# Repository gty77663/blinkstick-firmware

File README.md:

# BlinkStick Firmware

BlinkStick is a DIY open source USB RGB LED Controller. Original idea is to create a little & handy RGB stick, and make its code and protocol opensource, so everybody can enjoy playing with RGB LEDs using the programming launguage or application of your choise. It's small, the biggest model is the size of a credit card and supports both popular types of RGB LEDs - generic 12V ones and addressable WS2812. 

You can find more details about it here:

http://www.blinkstick.com

This branch contains the firmware,  required for the BlinkStick Pro, based around ATTiny45/85 chip.

- [BlinkStick Firmware](#blinkstick-firmware)
  - [BlinkStick types](#blinkstick-types)
  - [Serial number](#serial-number)
  - [BlinkStick communication protocol](#blinkstick-communication-protocol)
  - [EEPROM memory map](#eeprom-memory-map)
  - [How to build the firmware](#how-to-build-the-firmware)
    - [Windows](#windows)
    - [Linux](#linux)
    - [Mac-OS](#mac-os)
    - [Compiling](#compiling)
  - [TODO](#todo)
  - [License](#license)

## BlinkStick types
| Name                   | Description                                                                                                        | Link                                                          |
|------------------------|--------------------------------------------------------------------------------------------------------------------|---------------------------------------------------------------|
| BlinkStick             | Small formfactor of a USB stick with one WS2812 LED onboard, comes as a DIY kit.                                   | [here](https://www.blinkstick.com/products/blinkstick)        |
| BlinkStick Pro         | USB stick-sized controller board for generic RGB and WS2812 LED strips.                                            | [here](https://www.blinkstick.com/products/blinkstick-pro)    |
| BlinkStick Square      | Little handy square with 8 WS2812 LEDs and a micro-USB port.                                                       | [here](https://www.blinkstick.com/products/blinkstick-square) |
| BlinkStick Strip(mini) | Eight(4 for the mini version) WS2812LEDs shaped in one line & a micro-USB port.                                    | [here](https://www.blinkstick.com/products/blinkstick-strip)  |
| BlinkStick Nano        | Just like normal BlinkStick, but smaller, comes preassembled and has two WS2812 LEDs instead of one.               | [here](https://www.blinkstick.com/products/blinkstick-nano)   |
| BlinkStick Flex        | Really small formfactor with a micro-USB port that supports up to 32 WS2812 LEDs in a strip.                       | [here](https://www.blinkstick.com/products/blinkstick-flex)   |
| BlinkStick L3          | Combines BlinkStick Pro and LED Adapter to control normal, 12V RGB strips.                                         | [here](https://www.blinkstick.com/products/blinkstick-l3)     |
| BlinkStick Advanced    | Combines both generic RGB and WS2812 controllers in a very small formfactor to act as a universal LED strips tool. | none for now                                                  |

## Serial number
Each BlinkStick has a unique serial number 12-byte long serial number, that consist of "BS" header, that stands for "BlinksStick",
followed by its index number, 6 symbols length. The footer is 4 bytes long, that signify the BlinkStick version it is.  
Ex: BS123456-1.0  
```
BSnnnnnn-1.0
||  |    | |- Software minor version
||  |    |--- Software major version
||  |-------- Denotes sequential number
||----------- Denotes BlinkStick device
```
Possible BlinkStick version are:  
* 1.x - BlinkStick
* 2.x - BlinkStick Pro
* 3.x - BlinkStick Square/Strip/Nano/Flex   
This are differentiate by the device version, aka firmware version.  

| Version | Description       | N. of LEDs |
|---------|-------------------|------------|
| 0x200   | BlinkStick Square | 8          |
| 0x201   | BlinkStick Strip  | 8          |
| 0x202   | BlinkStick Nano   | 2          |
| 0x203   | BlinkStick Flex   | ≤32        |
* 4.x - BlinkStick Advanced

## BlinkStick communication protocol

BlinkStick is controller via HID USB reports, each report has its unique id and is responsible for its specific purpose:  

| Report ID | Description                                                                                                    | Format                      |
|-----------|----------------------------------------------------------------------------------------------------------------|-----------------------------|
| 1         | Set\get RGB strip color or first ARGB LED color on first channel                                               | [R, G, B]                   |
| 2         | Set\read the name of the BlinkStick                                                                            | [Binary Data 0..32]         |
| 3         | Set\read custom data stored in BlinkStick's EEPROM                                                             | [Binary Data 0..32]         |
| 4         | Set\read current mode: 0 - RGB LED Strip, 1 - Inverse RGB LED Strip, 2 - WS2812, 3 - Advanced (WS2812 and RGB) | [MODE]                      |
| 5         | Set\read the value of one single ARGB LED on specified channel with INDEX                                      | [CHANNEL, INDEX, R, G, B]   |
| 6         | Set\read LED  from 0 to x (x≤7), on specified channel                                                          | [Channel, [G, R, B][0..7]]  |
| 7         | Set\read LED colors from 0 to x (x≤15), on specified channel                                                   | [Channel, [G, R, B][0..15]] |
| 8         | Set\read LED colors from 0 to x (x≤31), on specified channel                                                   | [Channel, [G, R, B][0..31]] |
| 9         | Set\read LED colors from 0 to x (x≤63), on specified channel                                                   | [Channel, [G, R, B][0..63]] |

## EEPROM memory map 
BlinkStick uses EEPROM to store some of power sensitive data, such as its Name, Serial, etc. 
  
| Name             | Description |
|------------------|-------------|
| Address          | Use         |
| 0x00             | *unused*    |
| 0x01-0x0C        | **Serial**  |
| 0x0D             | **Mode**    |
| 0x0F-0x1F        | *unused*    |
| 0x20-0x3F        | **Name**    |
| 0x40-0x5F        | **Data**    |
| 0x60-0xFF(0x1ff) | *unused*    |

## How to build the firmware

### Windows   
* You'll need to install and add to system path [AVR-GCC toolchain](https://www.microchip.com/en-us/tools-resources/develop/microchip-studio/gcc-compilers)
* [Python3](https://www.python.org/downloads/)
* And [Make](https://www.gnu.org/software/make/#download) on you system. 

### Linux  
#### AVR-GCC toolchain  
    sudo apt-get update  
    sudo apt-get upgrade all
    sudo apt-get install gcc-avr binutils-avr avr-libc  

#### Python  
    sudo apt install python3 python3-pip
#### Make    
    sudo apt install make

### Mac-OS
#### AVR-GCC toolchain
First, you need to install HomeBrew:  

    ruby -e "$(curl -fsSL https://raw.githubusercontent.com/Homebrew/install/master/install)"

Then you can install avr toolchain, by typing two following commands:
First tap the repository:

    brew tap osx-cross/avr`

Then install the latest version of avr-libc (version 4.9.2 at the time of writing):

    brew install avr-libc

#### Python
You can download it from [python official site](https://www.python.org/downloads/macos/).

#### Make 
If you allready installed brew, paste this command in the terminal:

    brew install make

### Compiling
After installing all nessecery software, you can run make in project folder and choose one of the options that you need:
```
"This Makefile has no default rule. Use one of the following:"
"make hex ....... to build main.hex"
"make program ... to flash fuses and firmware"
"make fuse ...... to flash the fuses"
"make flash ..... to flash the firmware (use this on metaboard)"
"make dump ...... dump eeprom"
"make dumpflash . dump flash"
"make defaults .. write default eeprom"
"make clean ..... to delete objects and hex file"
"make deploy .... program, increment serial, defaults"
```

## TODO  
* Add BlinkStick devices support to SignalRGB
* Add BlinkStick devices support to OpenRGB
* Optional, maybe add built-in effects and animations, 

## License

Released under CC-BY-NC-SA 3.0 license:

http://creativecommons.org/licenses/by-nc-sa/3.0/

(c) 2013 by Agile Innovative Ltd  
(c) 2023 by gty77663

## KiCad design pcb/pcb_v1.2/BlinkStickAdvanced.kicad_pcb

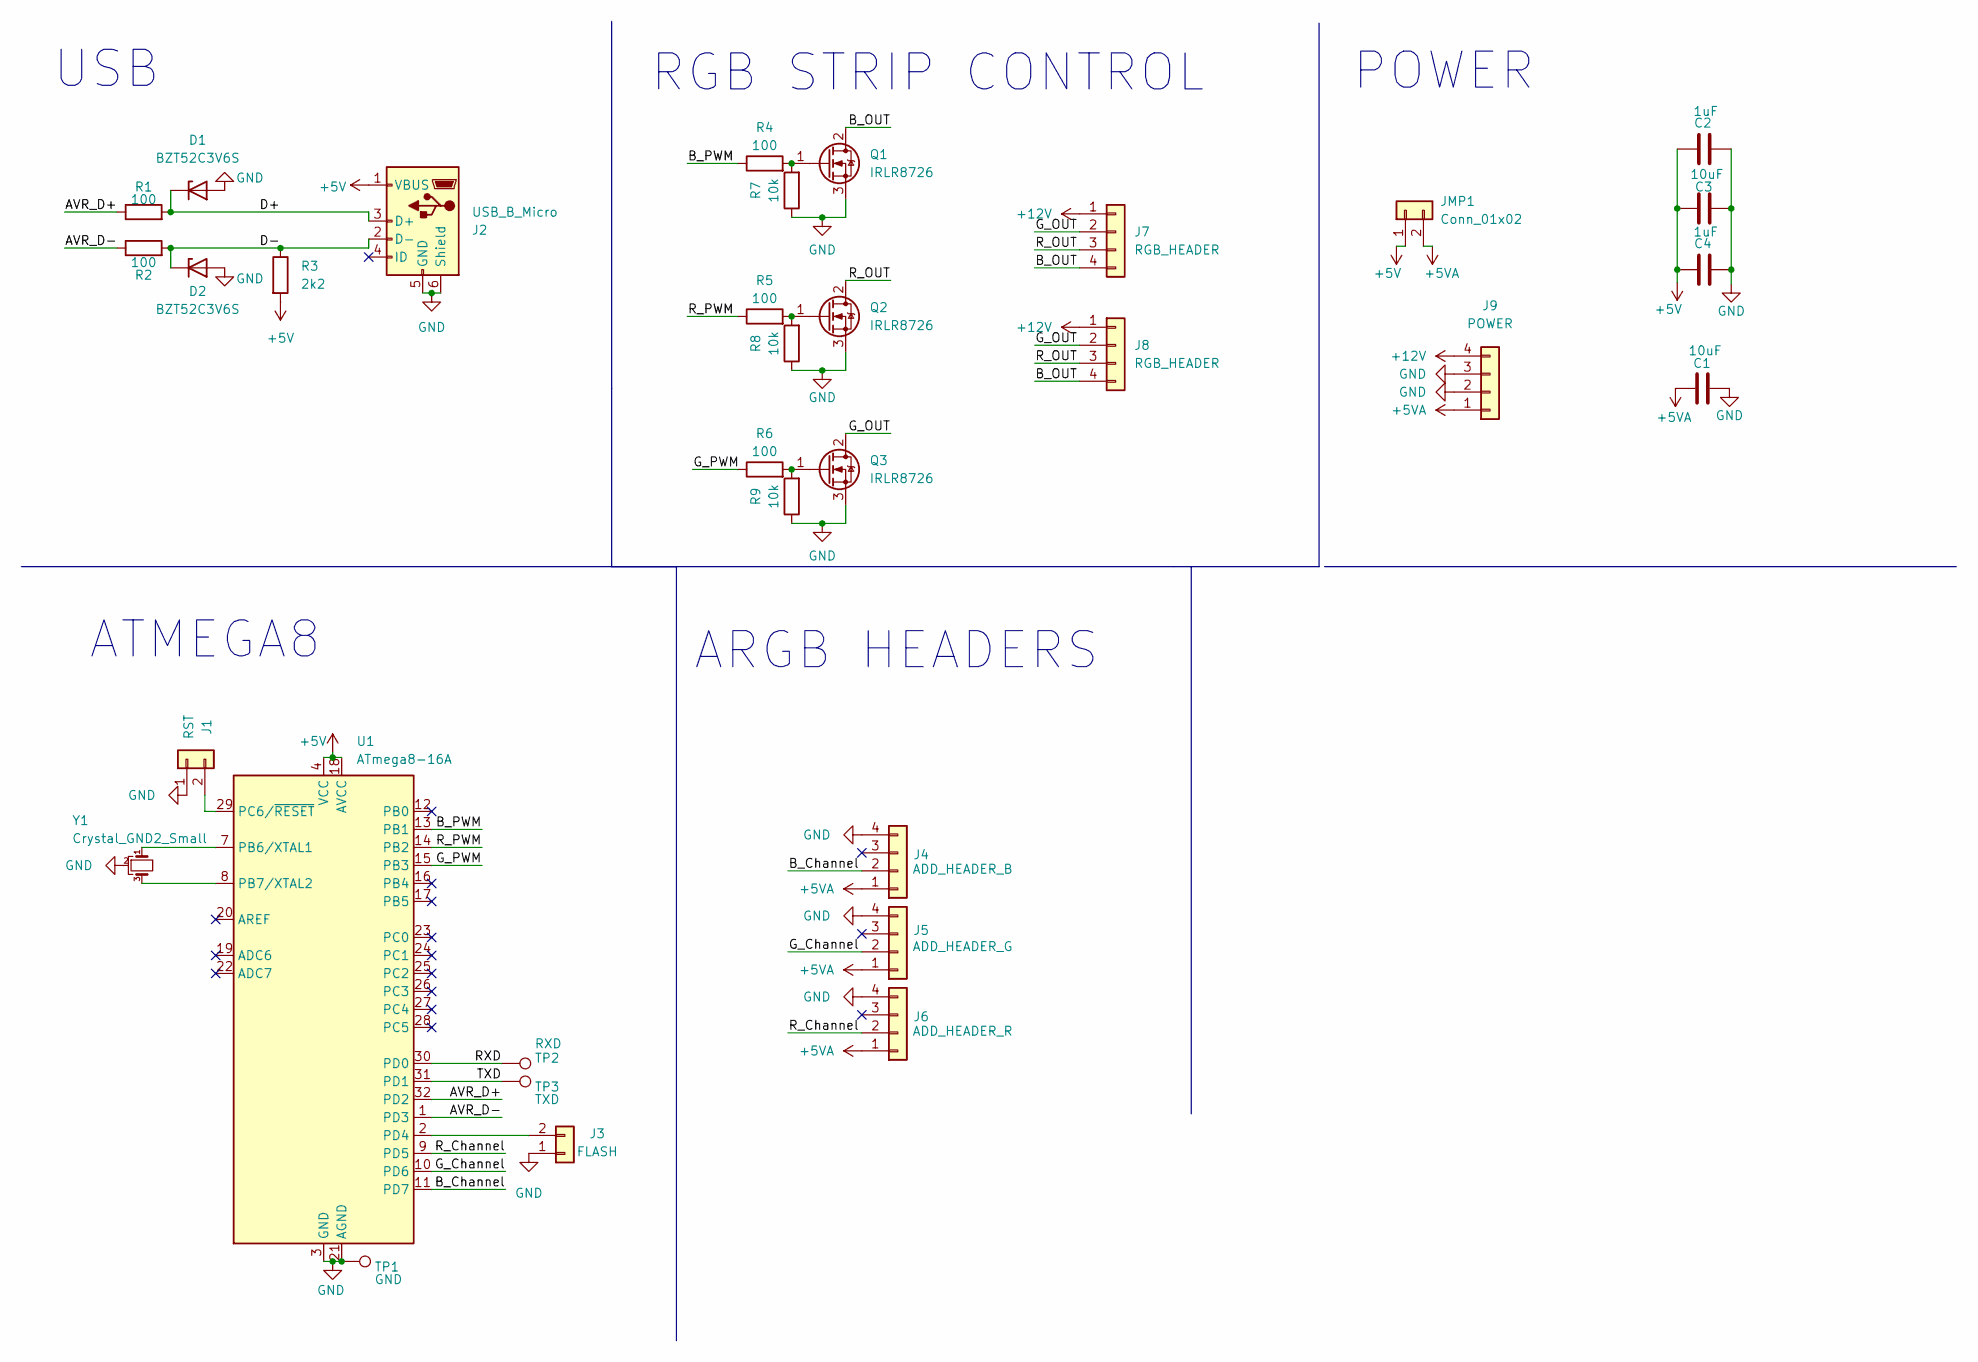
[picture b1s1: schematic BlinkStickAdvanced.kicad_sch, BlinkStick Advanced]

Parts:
C1, C3: 10uF; C_0603_1608Metric_Pad1.08x0.95mm_HandSolder
C2, C4: 1uF; C_0603_1608Metric_Pad1.08x0.95mm_HandSolder
D1, D2: BZT52C3V6S; D_SOD-323
J1: RST; PinHeader_1x02_P2.54mm_Vertical
J2: USB_B_Micro; USB_Micro-B_Molex-105017-0001
J3: FLASH; PinHeader_1x02_P2.54mm_Vertical
J4: ADD_HEADER_B; PinHeader_1x04_P2.54mm_Vertical
J5: ADD_HEADER_G; PinHeader_1x04_P2.54mm_Vertical
J6: ADD_HEADER_R; PinHeader_1x04_P2.54mm_Vertical
J7, J8: RGB_HEADER; PinHeader_1x04_P2.54mm_Vertical
J9: POWER; JST_XH_B4B-XH-A_1x04_P2.50mm_Vertical
JMP1: Conn_01x02; PinHeader_1x02_P2.54mm_Vertical
Q1, Q2, Q3: IRLR8726; TO-263-2
R1, R2, R4, R5, R6: 100; R_0603_1608Metric_Pad0.98x0.95mm_HandSolder
R3: 2k2; R_0603_1608Metric_Pad0.98x0.95mm_HandSolder
R7, R8, R9: 10k; R_0603_1608Metric_Pad0.98x0.95mm_HandSolder
TP1: GND; TestPoint_Pad_D1.5mm
TP2: RXD; TestPoint_Pad_D1.5mm
TP3: TXD; TestPoint_Pad_D1.5mm
U1: ATmega8-16A; TQFP-32_7x7mm_P0.8mm
Y1: Crystal_GND2_Small; Resonator_SMD_Murata_CSTxExxV-3Pin_3.0x1.1mm

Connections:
+5V: C2.2, C3.2, C4.2, J2.1 (VBUS), JMP1.1, R3.2, U1.4 (VCC), U1.6 (VCC), U1.18 (AVCC)
+5VA: C1.2, J4.1, J5.1, J6.1, J9.1, JMP1.2
+12V: J7.1, J8.1, J9.4
/AVR_D+: R1.1, U1.32 (PD2)
/AVR_D-: R2.1, U1.1 (PD3)
/B_Channel: J4.2, U1.11 (PD7)
/B_OUT: J7.4, J8.4, Q1.2 (D)
/B_PWM: R4.1, U1.13 (PB1)
/D+: D1.1 (K), J2.3 (D+), R1.2
/D-: D2.1 (K), J2.2 (D-), R2.2, R3.1
/G_Channel: J5.2, U1.10 (PD6)
/G_OUT: J7.2, J8.2, Q3.2 (D)
/G_PWM: R6.1, U1.15 (PB3)
/RXD: TP2.1, U1.30 (PD0)
/R_Channel: J6.2, U1.9 (PD5)
/R_OUT: J7.3, J8.3, Q2.2 (D)
/R_PWM: R5.1, U1.14 (PB2)
/TXD: TP3.1, U1.31 (PD1)
GND: C1.1, C2.1, C3.1, C4.1, D1.2 (A), D2.2 (A), J1.1, J2.5 (GND), J2.6 (Shield), J3.1, J4.4, J5.4, J6.4, J9.2, J9.3, Q1.3 (S), Q2.3 (S), Q3.3 (S), R7.1, R8.1, R9.1, TP1.1, U1.3 (GND), U1.5 (GND), U1.21 (AGND), Y1.2
unnamed: Q1.1 (G), R4.2, R7.2
unnamed: Q2.1 (G), R5.2, R8.2
unnamed: Q3.1 (G), R6.2, R9.2
unnamed: J3.2, U1.2 (PD4)
unnamed: U1.7 (PB6/XTAL1), Y1.1
unnamed: U1.8 (PB7/XTAL2), Y1.3
unnamed: J1.2, U1.29 (PC6/~RESET)

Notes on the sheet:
RGB STRIP CONTROL
POWER
ATMEGA8
USB
ARGB HEADERS

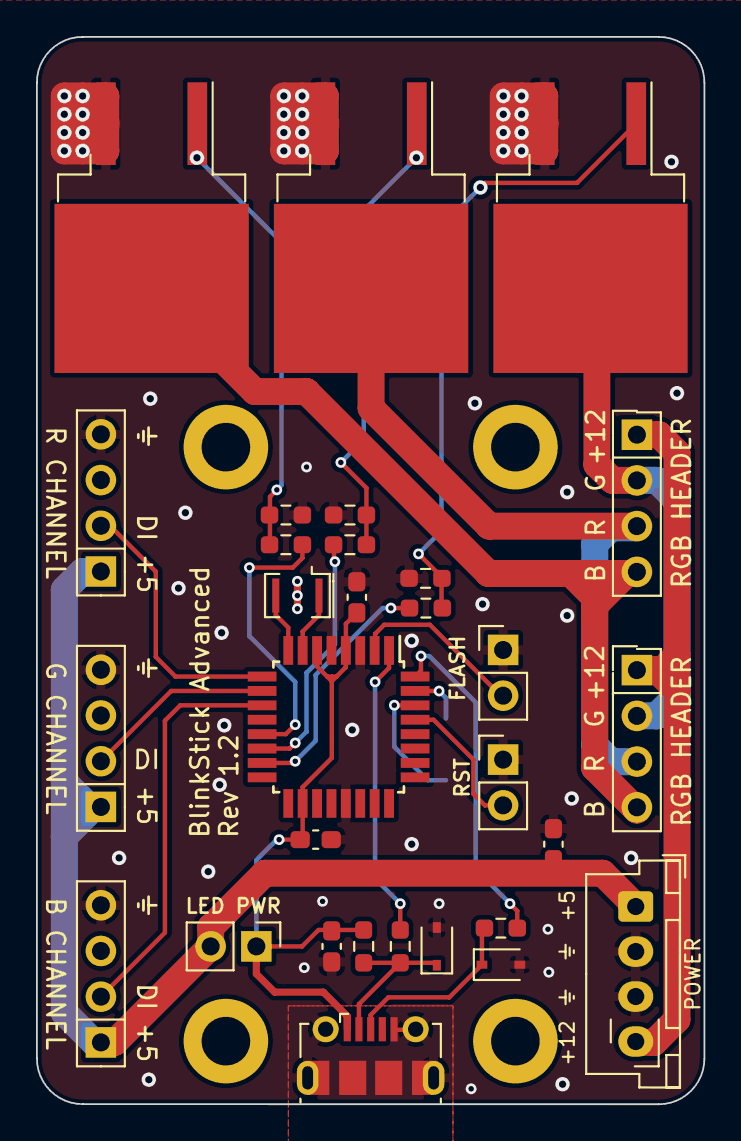
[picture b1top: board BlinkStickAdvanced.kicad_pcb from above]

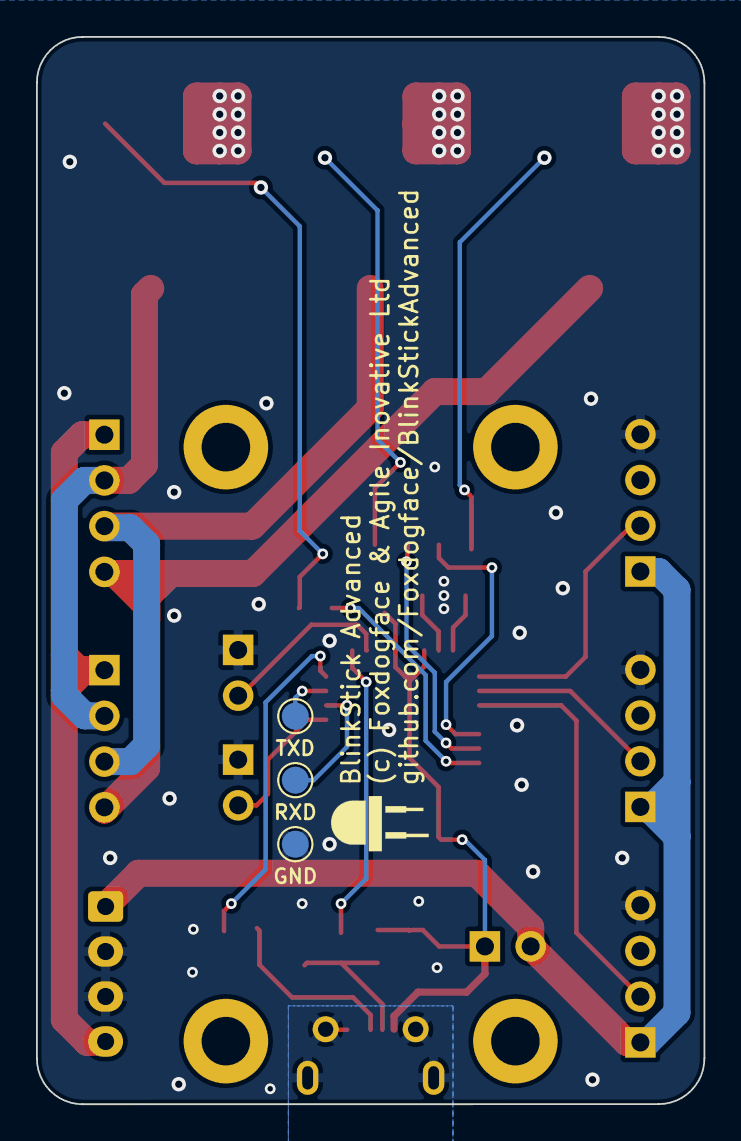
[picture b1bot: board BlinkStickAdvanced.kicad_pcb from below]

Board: 2 copper layers, 37.1 x 59.3 mm, 33 parts (3 on the bottom side), 26 nets.

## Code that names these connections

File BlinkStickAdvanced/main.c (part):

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
#define LED_ADDR_PORT_DDR        DDRD

#define R_ADDR_BIT               PD5
#define G_ADDR_BIT               PD6
#define B_ADDR_BIT               PD7

#define LED_RGB_PORT_DDR		DDRB

#define R_PWM					OCR1B
#define G_PWM					OCR2
#define B_PWM					OCR1A

#define MODE_RGB			0
#define MODE_RGB_INVERSE   	1
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	
	//Set LED ports to output
    LED_ADDR_PORT_DDR |= _BV(R_ADDR_BIT) | _BV(G_ADDR_BIT) | _BV(B_ADDR_BIT);
	LED_RGB_PORT_DDR  |= _BV(PB3) | _BV(PB2) | _BV(PB1);

	ApplyMode();

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
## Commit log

2023-01-23 PCB Change Silkscreen
2023-01-24 .gitignore Update
2023-03-09 Add USBaspLoader support.
2023-03-09 USBaspLoader support for PCB.
2023-08-18 Add new PCB version with right-angled connectors instead of straight ones.
2023-08-18 Move old PCB files to a different folder.
2023-08-18 Update the README
2023-08-18 Small changes & bug fixes.

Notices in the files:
BlinkStickAdvanced/main.c:
Copyright: (c) 2013 by Agile Innovative Ltd
License: GNU GPL v2 (see License.txt), GNU GPL v3 or proprietary (CommercialLicense.txt)
